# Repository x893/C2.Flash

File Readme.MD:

Implement Silabs C2 flash programming protocol via NUCLEO-103RB, Arduino and EFM32ZG STK-3200 boards.
See https://www.silabs.com/Support%20Documents/TechnicalDocs/an127.pdf
and http://akb77.com/g/silabs/jump-to-silabs-step-1/ for details

Port AN127SW to NUCLEO-103RB
Add SendC2.exe command line utility to upload hex file to USB-DA
All timing tune for 72MHz CPU system clock.
Implement terminal mode for C8051 commands.
1.	C2CK	- PC8
2.	C2D		- PC9
	Use Morpho Headers to connect

1. Upload C2_Flash.pde sketch to Arduino
2. Start program C2.Flash.exe (need .NET 2.0)
    Target        Arduino        Atmel
      C2CK      - digital pin 5 (PortD 5)
      C2D       - digital pin 6 (PortD 6)
      GND       - GND

Port AN127SW to EFM32-STK3700
1. Connect
    Target        EFM32GG STK-3700
      C2D       - PC3
      C2CK      - PC0
      GND       - GND

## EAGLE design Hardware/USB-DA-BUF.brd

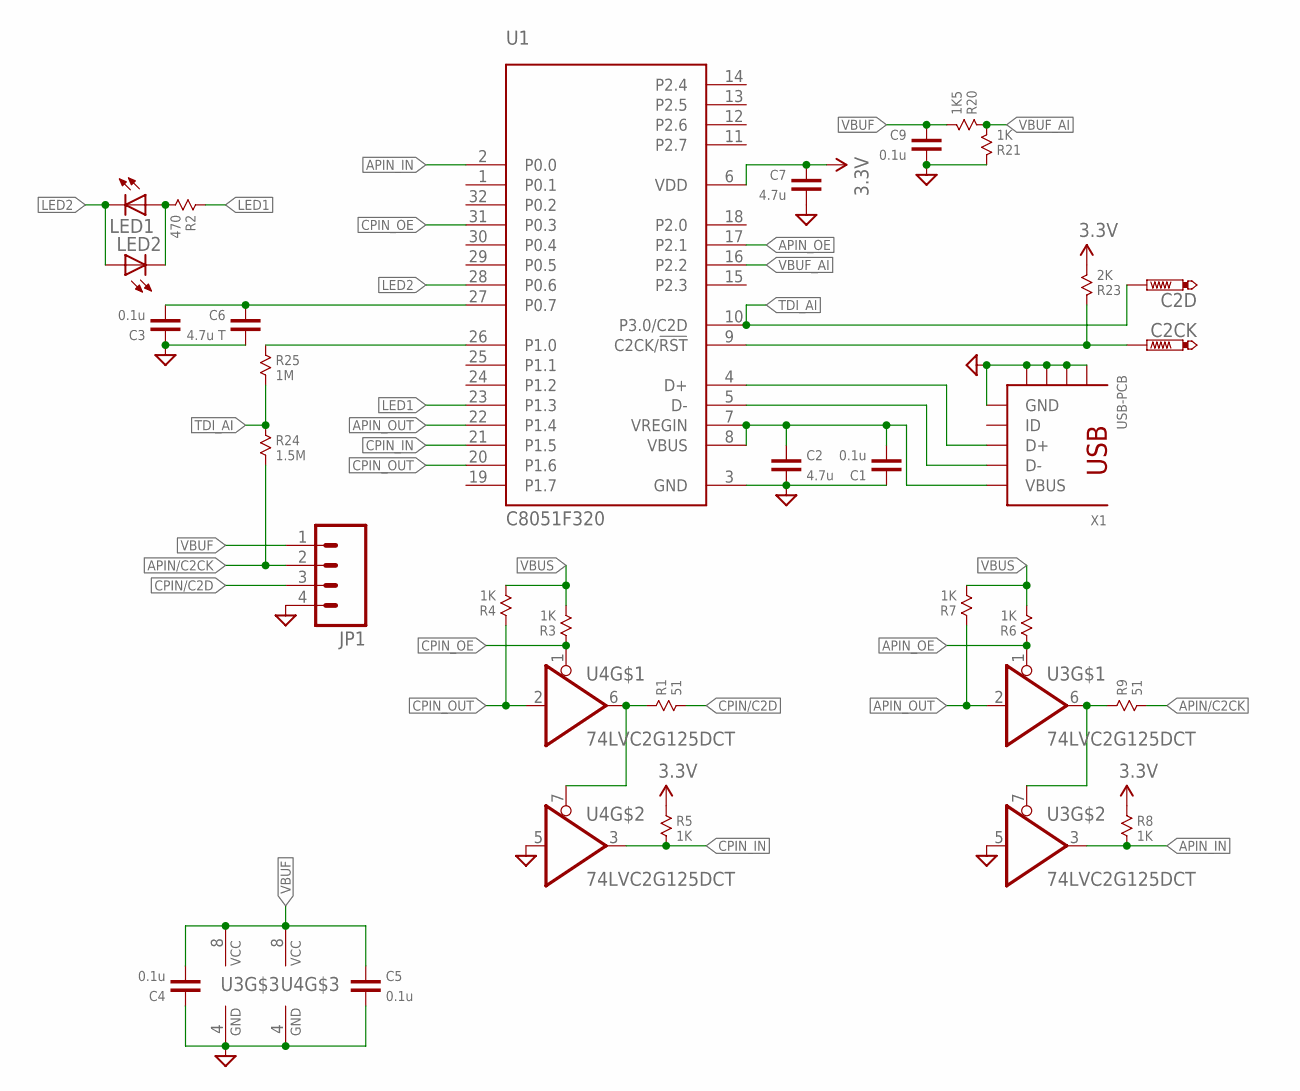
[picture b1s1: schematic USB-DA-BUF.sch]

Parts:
C1, C3, C4, C5, C9: 0.1u; 0603
C2, C7: 4.7u; 0603
C2CK, C2D: PTR1TP10R; TP10R
C6: 4.7u T; 0603
JP1: M04PTH; 1X04
LED1, LED2: LED0603; LED-0603
R1, R9: 51; 0603
R2: 470; 0603
R3, R4, R5, R6, R7, R8, R21: 1K; 0603
R20: 1K5; 0603
R23: 2K; 0603
R24: 1.5M; 0603
R25: 1M; 0603
U1: C8051F320; LQFP32
U3, U4: 74LVC2G125DCT; SSOP08
X1: USB-PCB; USB-MINIB

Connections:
3.3V: C7.2, R5.1, R8.1, R23.2, U1.6 (VDD)
APIN/C2CK: JP1.2, R9.2, R24.2
APIN_IN: R8.2, U1.2 (P0.0), U3.3 (O)
APIN_OE: R6.1, U1.17 (P2.1), U3.1 (OE)
APIN_OUT: R7.1, U1.22 (P1.4), U3.2 (I)
CPIN/C2D: JP1.3, R1.2
CPIN_IN: R5.2, U1.21 (P1.5), U4.3 (O)
CPIN_OE: R3.1, U1.31 (P0.3), U4.1 (OE)
CPIN_OUT: R4.1, U1.20 (P1.6), U4.2 (I)
GND: C1.2, C2.1, C3.2, C4.2, C5.1, C6.1, C7.1, C9.1, JP1.4, R21.1, U1.3 (GND), U3.4 (GND), U3.5 (I), U4.4 (GND), U4.5 (I), X1.GND, X1.GND@1 (GND), X1.GND@2 (GND), X1.GND@3 (GND), X1.GND@4 (GND)
LED1: R2.1, U1.23 (P1.3)
LED2: LED1.C, LED2.A, U1.28 (P0.6)
unnamed: U1.4 (D+), X1.D+
unnamed: U1.5 (D-), X1.D-
unnamed: R1.1, U4.6 (O), U4.7 (OE)
unnamed: LED1.A, LED2.C, R2.2
unnamed: R9.1, U3.6 (O), U3.7 (OE)
P0.7: C3.1, C6.2, U1.27 (P0.7)
P1.0: R25.1, U1.26 (P1.0)
RST: C2CK.TP, R23.1, U1.9 (C2CK/!RST)
TDI_AI: C2D.TP, R24.1, R25.2, U1.10 (P3.0/C2D)
VBUF: C4.1, C5.2, C9.2, JP1.1, R20.2, U3.8 (VCC), U4.8 (VCC)
VBUF_AI: R20.1, R21.2, U1.16 (P2.2)
VBUS: C1.1, C2.2, R3.2, R4.2, R6.2, R7.2, U1.7 (VREGIN), U1.8 (VBUS), X1.VBUS

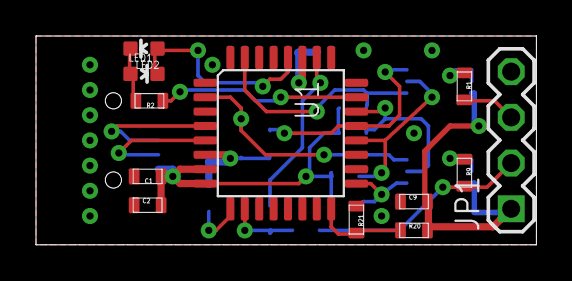
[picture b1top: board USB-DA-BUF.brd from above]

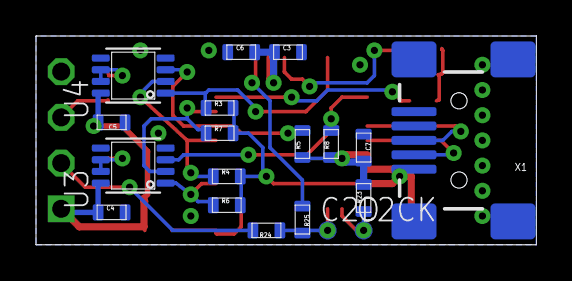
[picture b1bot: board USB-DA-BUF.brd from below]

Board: 2 copper layers, 27.8 x 11.6 mm, 31 parts (19 on the bottom side), 24 nets.

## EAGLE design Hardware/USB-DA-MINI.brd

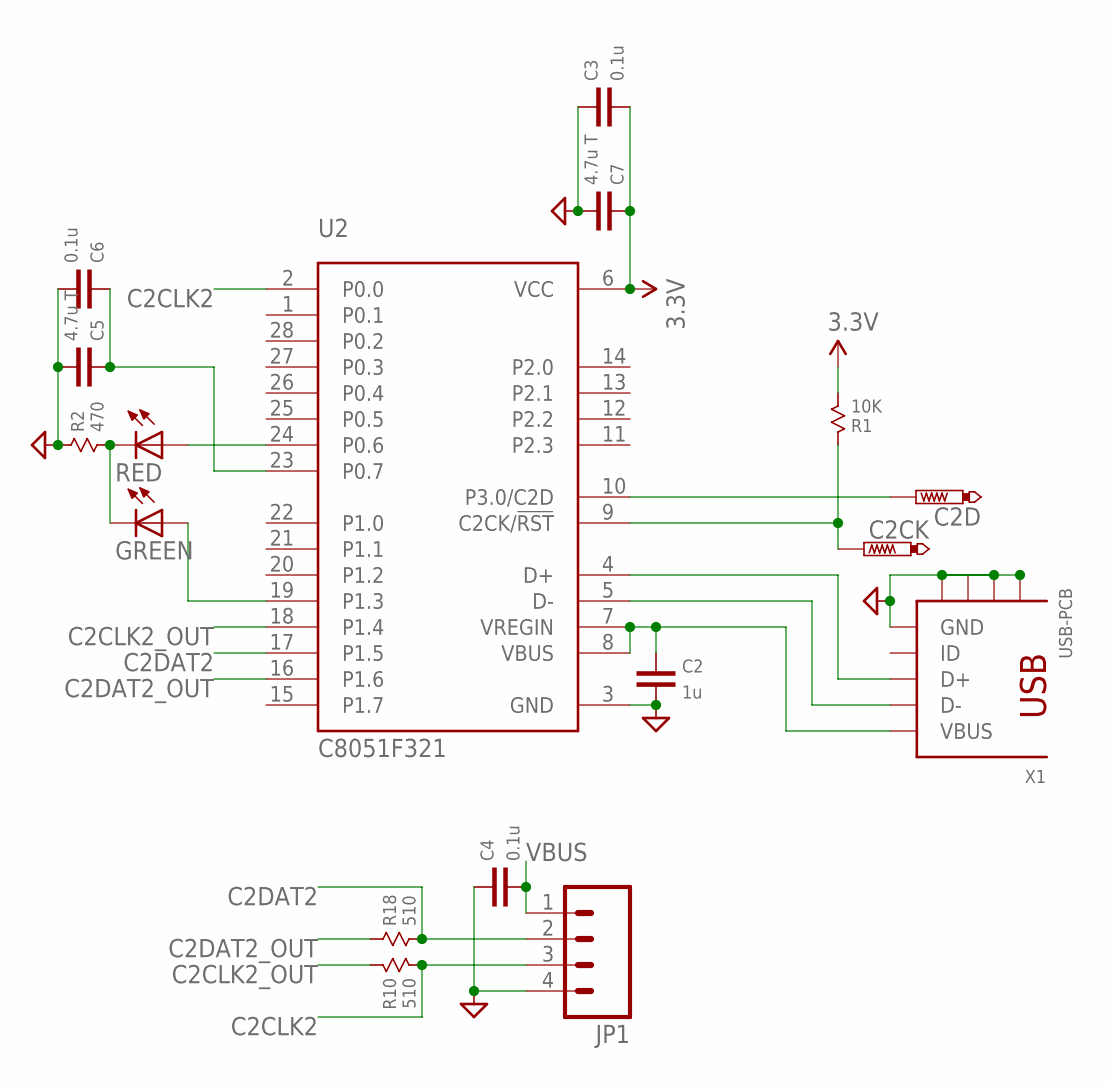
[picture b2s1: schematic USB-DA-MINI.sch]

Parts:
C2: 1u; 0603
C2CK, C2D: PTR1B1,27; B1,27
C3, C4, C6: 0.1u; 0603
C5, C7: 4.7u T; 0603
GREEN: LED0603; LED-0603
JP1: M04PTH; 1X04
R1: 10K; 0603
R2: 470; 0603
R10, R18: 510; 0603
RED: LED0603; LED-0603
U2: C8051F321; QFN28-5X5
X1: USB-PCB; USB-MINIB

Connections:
3.3V: C3.1, C7.2, R1.2, U2.6 (VCC)
C2CLK2: JP1.3, R10.2, U2.2 (P0.0)
C2CLK2_OUT: R10.1, U2.18 (P1.4)
C2DAT2: JP1.2, R18.2, U2.17 (P1.5)
C2DAT2_OUT: R18.1, U2.16 (P1.6)
D+: U2.4 (D+), X1.D+
D-: U2.5 (D-), X1.D-
GND: C2.1, C3.2, C4.2, C5.1, C6.1, C7.1, JP1.4, R2.1, U2.3 (GND), X1.GND, X1.GND@1 (GND), X1.GND@2 (GND), X1.GND@3 (GND), X1.GND@4 (GND)
LED_GREEN: GREEN.A, U2.19 (P1.3)
LED_RED: RED.A, U2.24 (P0.6)
unnamed: C5.2, C6.2, U2.23 (P0.7)
unnamed: GREEN.C, R2.2, RED.C
RST: C2CK.TP, R1.1, U2.9 (C2CK/!RST)
TDI_AI: C2D.TP, U2.10 (P3.0/C2D)
VBUS: C2.2, C4.1, JP1.1, U2.7 (VREGIN), U2.8 (VBUS), X1.VBUS

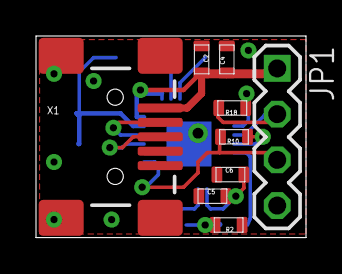
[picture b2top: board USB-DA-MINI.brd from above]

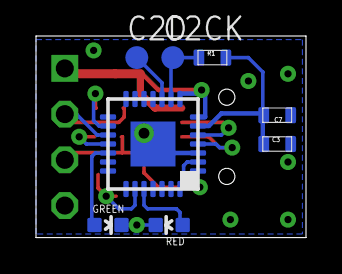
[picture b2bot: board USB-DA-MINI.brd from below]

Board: 2 copper layers, 15.0 x 11.2 mm, 17 parts (8 on the bottom side), 15 nets.

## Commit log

2013-02-03 Add Readme
2013-06-26 Cosmetic changes
2014-02-27 Add EFM32ZG STK-3200 to emulate C2 protocol
2014-04-11 Port AN127SW to EFM32-STK3700
2014-04-11 Change pins for C2CK/CD for STK-3700
2014-04-11 Project fix
2014-04-11 Add EFM32-Cdc.inf for EFM32 CDC
2014-04-11 Change Readme
2014-04-12 Fix buffer overflow
2014-04-13 Fix batch command processing
2014-04-13 Fix back char oricess
2014-04-25 Fix issues
2014-05-01 no message
2014-07-06 Port to NUCLEO-103RB, add USB-DA hardware and firmware
2014-07-12 Add pins for NUCLEO-103RB
2014-07-17 Typo C2_Flash.pde
    SI100X_DEVICEID was misspelled.
2015-02-07 EFM32 STK-3700 support
